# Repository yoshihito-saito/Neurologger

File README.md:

# WILD

**WILD** (Wireless, Interactive, Lightweight Datalogger) is an ultra-lightweight multimodal neurologger for long-term neural and behavioral recording in freely behaving animals. It combines local neural data logging, behavioral sensing, onboard processing, and responsive stimulation in a head-mounted platform designed for naturalistic and multi-animal experiments.

## Documentation

The documentation portal is built with MkDocs Material and is maintained through Markdown files in [`docs/`](docs/).

- [Getting Started](docs/getting-started/index.md)
- [Hardware](docs/hardware/index.md)
- [Software](docs/software/index.md)
- [Analysis](docs/analysis/index.md)
- [Community](docs/contributing.md)

## Platform Scope

- Local microSD electrophysiology recording with BLE-based control, synchronization, status, and low-bandwidth preview
- Closed-loop stimulation through embedded DSP and curated TinyML pipelines
- Current open-source 64-channel workflows, with Neuropixels-compatible and active-probe variants documented separately as research targets
- IMU, ultrasonic audio, camera, and digital event recording
- TinyML inference support through validated release-integrated models
- Long-term recording and multi-animal experiment workflows

## Repository Layout

| Path | Purpose |
| --- | --- |
| [`docs/`](docs/) | MkDocs documentation source |
| [Latest GitHub release](https://github.com/ayalab1/Neurologger/releases/latest) | Prebuilt device release images |
| [`Software/`](Software/) | WILD Console installers |
| [`Code/`](Code/) | MATLAB and Python analysis scripts |
| [`PCB/`](PCB/) | PCB fabrication and assembly files |
| [`3Dprint/`](3Dprint/) | Mechanical parts and CAD files |

## Local Documentation Build

```bash
pip install -r requirements.txt
mkdocs serve
```

The GitHub Pages workflow builds the site with:

```bash
mkdocs build --strict
```

## License

See [LICENSE](LICENSE).

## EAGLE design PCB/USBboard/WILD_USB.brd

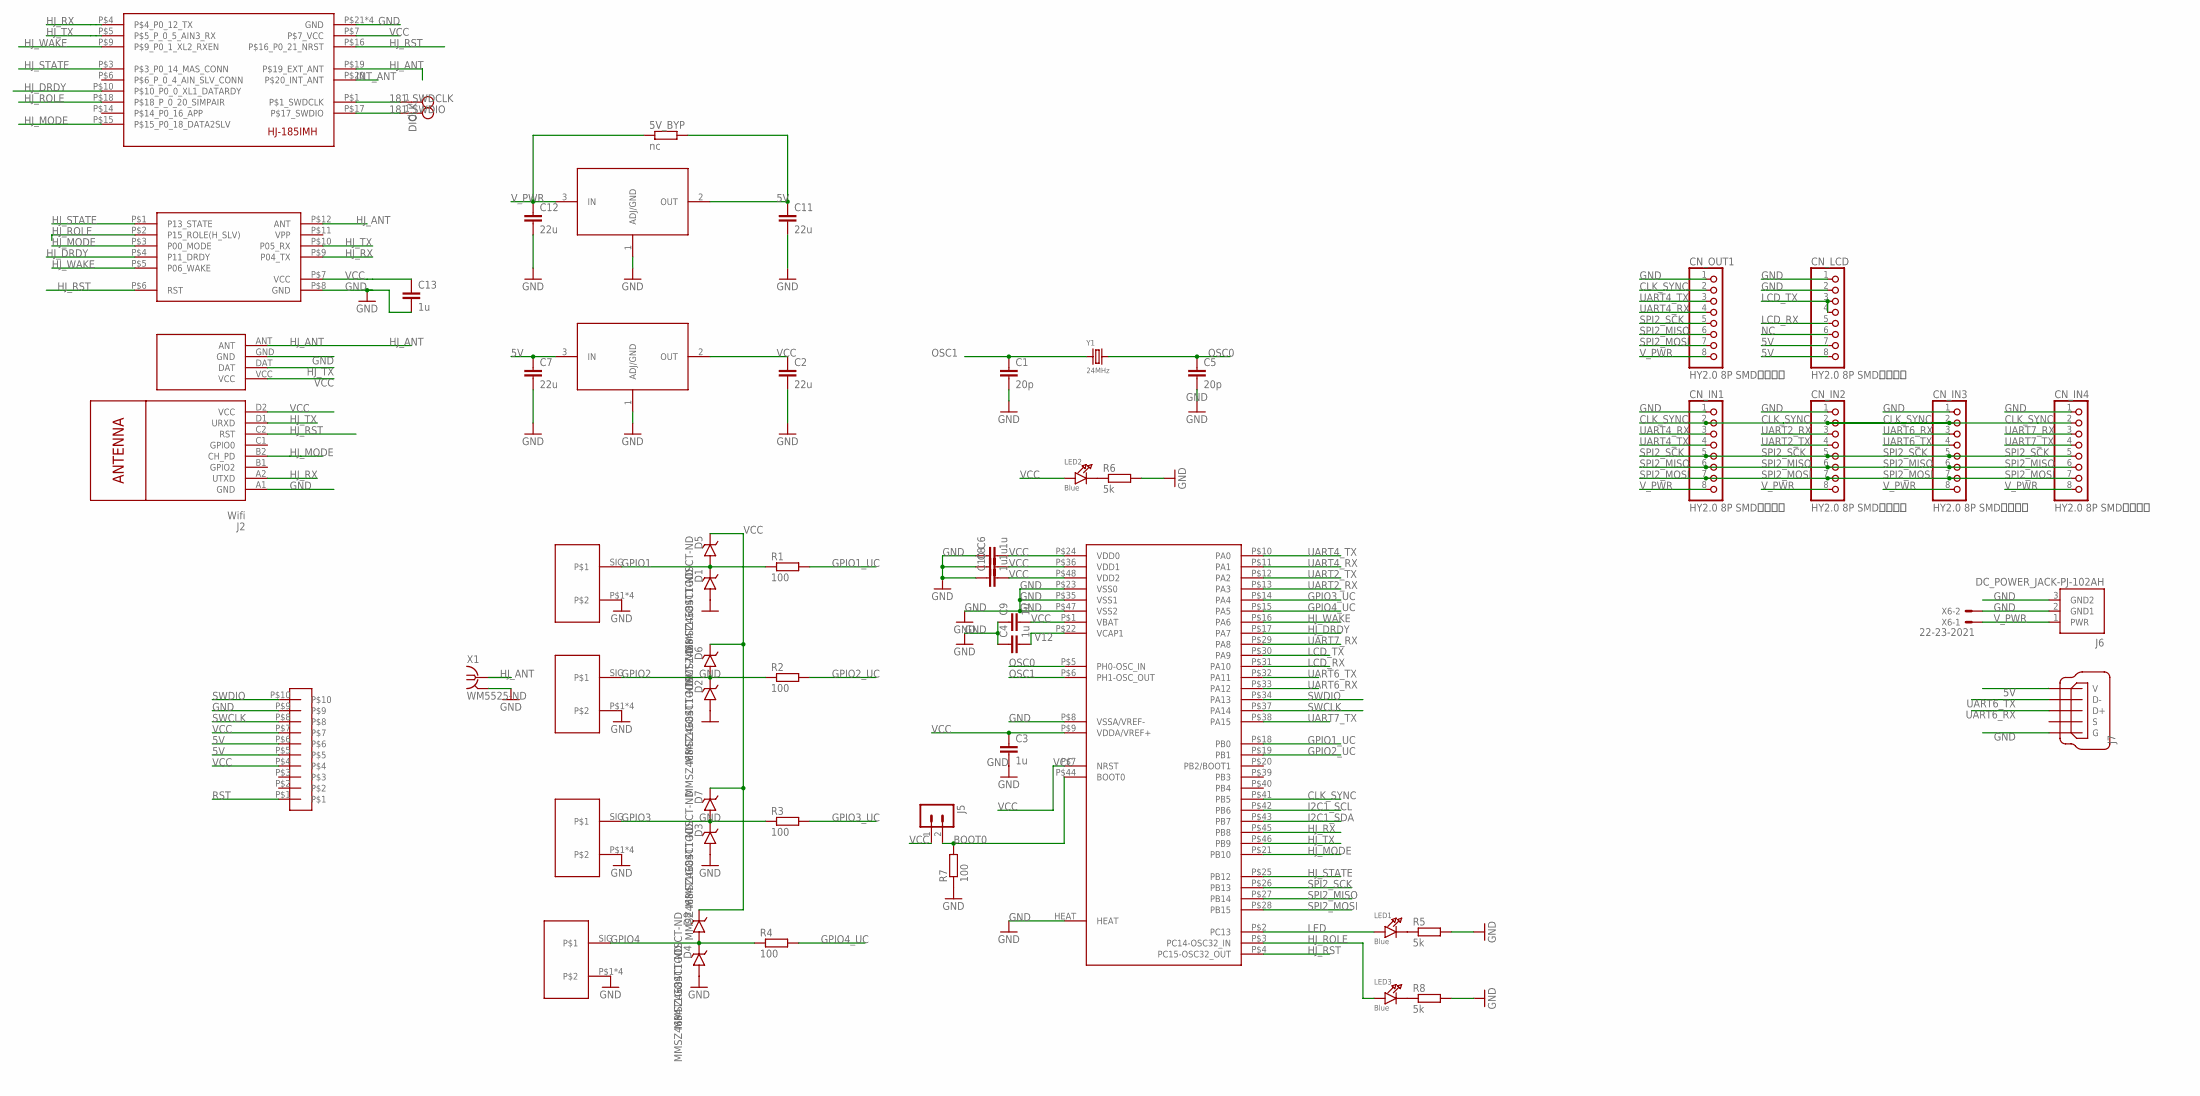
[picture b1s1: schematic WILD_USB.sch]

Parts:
5V_BYP: nc; R1206
C1, C5: 20p; C1206
C2, C7, C11, C12: 22u; C1206
C3, C4, C6, C8, C9, C10, C13: 1u; C1206
CLK: TESTPOINT_SMALL
CN_IN1, CN_IN2, CN_IN3, CN_IN4: HY2.0 8P SMD卧贴插座; JSTPH8
CN_LCD: HY2.0 8P SMD卧贴插座; JSTPH8
CN_OUT1: HY2.0 8P SMD卧贴插座; JSTPH8
D1, D2, D3, D4, D5, D6, D7, D8: MMSZ4684T1GOSCT-ND; SOD-123
DIO: TESTPOINT_SMALL
J1: Sub-GHz; SYN115
J2: Wifi; WIRELESS-WIFI-ESP-01
J3: 2*5P 2.54mm 双排母 母座; 2.54MM_2X5
J5: nc; JUMPER2
J6: DC_POWER_JACK-PJ-102AH; PJ-102AH
J7: J7; ZX62R-B-5P
LED1, LED2, LED3: Blue; CHIPLED_1206
R1, R2, R3, R4, R7: 100; R1206
R5, R6, R8: 5k; R1206
U1: STM32F413CHU6; UFQFPN48
U2: HJ580
U3: HJ_185IMHQFN; HJ_185IMH
U4: ADP3338AKCZ-3.3; SOT223
U5: nc; SOT223
X1: WM5525-ND; BU-SMA-H
X2, X3, X4, X5: BNC_8MM; BNC_V_8MM
X6: 22-23-2021
Y1: 24MHz; HC49UP

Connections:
5V: 5V_BYP.2, C7.1, C11.1, CN_LCD.7, CN_LCD.8, J3.P$5, J3.P$6, J7.1 (V), U4.3 (IN), U5.2 (OUT)
181_SWDCLK: CLK.1, U3.P$1 (P$1_SWDCLK)
181_SWDIO: DIO.1, U3.P$17 (P$17_SWDIO)
BOOT0: J5.2, R7.2, U1.P$44 (BOOT0)
CLK_SYNC: CN_IN1.2, CN_IN2.2, CN_IN3.2, CN_IN4.2, CN_OUT1.2, U1.P$41 (PB5)
GND: C1.2, C2.2, C3.2, C4.1, C5.2, C6.1, C7.2, C8.1, C9.1, C10.1, C11.2, C12.2, C13.2, CN_IN1.1, CN_IN2.1, CN_IN3.1, CN_IN4.1, CN_LCD.1, CN_LCD.2, CN_OUT1.1, D1.2 (A), D2.2 (A), D3.2 (A), D4.2 (A), J1.GND, J2.A1 (GND), J3.P$9, J6.2 (GND1), J6.3 (GND2), J7.5 (G), R5.2, R6.2, R7.1, R8.2, U1.HEAT, U1.P$8 (VSSA/VREF-), U1.P$23 (VSS0), U1.P$35 (VSS1), U1.P$47 (VSS2), U2.P$8 (GND), U3.P$21 (GND), U3.P$22 (GND), U3.P$23 (GND), U3.P$24 (GND), U4.1 (ADJ/GND), U5.1 (ADJ/GND), X1.2, X1.3 (2), X1.4 (2), X1.5 (2), X2.P$1, X2.P$2, X2.P$3, X2.P$4, X3.P$1, X3.P$2, X3.P$3, X3.P$4, X4.P$1, X4.P$2, X4.P$3, X4.P$4, X5.P$1, X5.P$2, X5.P$3, X5.P$4, X6.2
GPIO1: D1.1 (C), D5.2 (A), R1.1, X2.SIG
GPIO1_UC: R1.2, U1.P$18 (PB0)
GPIO2: D2.1 (C), D6.2 (A), R2.1, X3.SIG
GPIO2_UC: R2.2, U1.P$19 (PB1)
GPIO3: D3.1 (C), D7.2 (A), R3.1, X4.SIG
GPIO3_UC: R3.2, U1.P$14 (PA4)
GPIO4: D4.1 (C), D8.2 (A), R4.1, X5.SIG
GPIO4_UC: R4.2, U1.P$15 (PA5)
HJ_ANT: J1.ANT, U2.P$12 (ANT), U3.P$19 (P$19_EXT_ANT), X1.1
HJ_DRDY: U1.P$17 (PA7), U2.P$4 (P11_DRDY), U3.P$10 (P$10_P0_0_XL1_DATARDY)
HJ_MODE: J2.B2 (CH_PD), U1.P$21 (PB10), U2.P$3 (P00_MODE), U3.P$15 (P$15_P0_18_DATA2SLV)
HJ_ROLE: LED3.A, U1.P$3 (PC14-OSC32_IN), U2.P$2 (P15_ROLE(H_SLV)), U3.P$18 (P$18_P_0_20_SIMPAIR)
HJ_RST: J2.C2 (RST), U1.P$4 (PC15-OSC32_OUT), U2.P$6 (RST), U3.P$16 (P$16_P0_21_NRST)
HJ_RX: J2.A2 (UTXD), U1.P$45 (PB8), U2.P$9 (P04_TX), U3.P$4 (P$4_P0_12_TX)
HJ_STATE: U1.P$25 (PB12), U2.P$1 (P13_STATE), U3.P$3 (P$3_P0_14_MAS_CONN)
HJ_TX: J1.DAT, J2.D1 (URXD), U1.P$46 (PB9), U2.P$10 (P05_RX), U3.P$5 (P$5_P_0_5_AIN3_RX)
HJ_WAKE: U1.P$16 (PA6), U2.P$5 (P06_WAKE), U3.P$9 (P$9_P0_1_XL2_RXEN)
I2C1_SCL: U1.P$42 (PB6)
I2C1_SDA: U1.P$43 (PB7)
INT_ANT: U3.P$20 (P$20_INT_ANT)
LCD_RX: CN_LCD.5, U1.P$31 (PA10)
LCD_TX: CN_LCD.3, CN_LCD.4, U1.P$30 (PA9)
LED: LED1.A, U1.P$2 (PC13)
unnamed: LED3.C, R8.1
unnamed: LED1.C, R5.1
unnamed: LED2.C, R6.1
NC: CN_LCD.6
OSC0: C5.1, U1.P$5 (PH0-OSC_IN), Y1.2
OSC1: C1.1, U1.P$6 (PH1-OSC_OUT), Y1.1
RST: J3.P$1
SPI2_MISO: CN_IN1.6, CN_IN2.6, CN_IN3.6, CN_IN4.6, CN_OUT1.6, U1.P$27 (PB14)
SPI2_MOSI: CN_IN1.7, CN_IN2.7, CN_IN3.7, CN_IN4.7, CN_OUT1.7, U1.P$28 (PB15)
SPI2_SCK: CN_IN1.5, CN_IN2.5, CN_IN3.5, CN_IN4.5, CN_OUT1.5, U1.P$26 (PB13)
SWCLK: J3.P$8, U1.P$37 (PA14)
SWDIO: J3.P$10, U1.P$34 (PA13)
UART2_RX: CN_IN2.3, U1.P$13 (PA3)
UART2_TX: CN_IN2.4, U1.P$12 (PA2)
UART4_RX: CN_IN1.3, CN_OUT1.4, U1.P$11 (PA1)
UART4_TX: CN_IN1.4, CN_OUT1.3, U1.P$10 (PA0)
UART6_RX: CN_IN3.3, J7.3 (D+), U1.P$33 (PA12)
UART6_TX: CN_IN3.4, J7.2 (D-), U1.P$32 (PA11)
UART7_RX: CN_IN4.3, U1.P$29 (PA8)
UART7_TX: CN_IN4.4, U1.P$38 (PA15)
V12: C4.2, U1.P$22 (VCAP1)
VCC: C2.1, C3.1, C6.2, C8.2, C9.2, C10.2, C13.1, D5.1 (C), D6.1 (C), D7.1 (C), D8.1 (C), J1.VCC, J2.D2 (VCC), J3.P$4, J3.P$7, J5.1, LED2.A, U1.P$1 (VBAT), U1.P$7 (NRST), U1.P$9 (VDDA/VREF+), U1.P$24 (VDD0), U1.P$36 (VDD1), U1.P$48 (VDD2), U2.P$7 (VCC), U3.P$7 (P$7_VCC), U4.2 (OUT)
V_PWR: 5V_BYP.1, C12.1, CN_IN1.8, CN_IN2.8, CN_IN3.8, CN_IN4.8, CN_OUT1.8, J6.1 (PWR), U5.3 (IN), X6.1

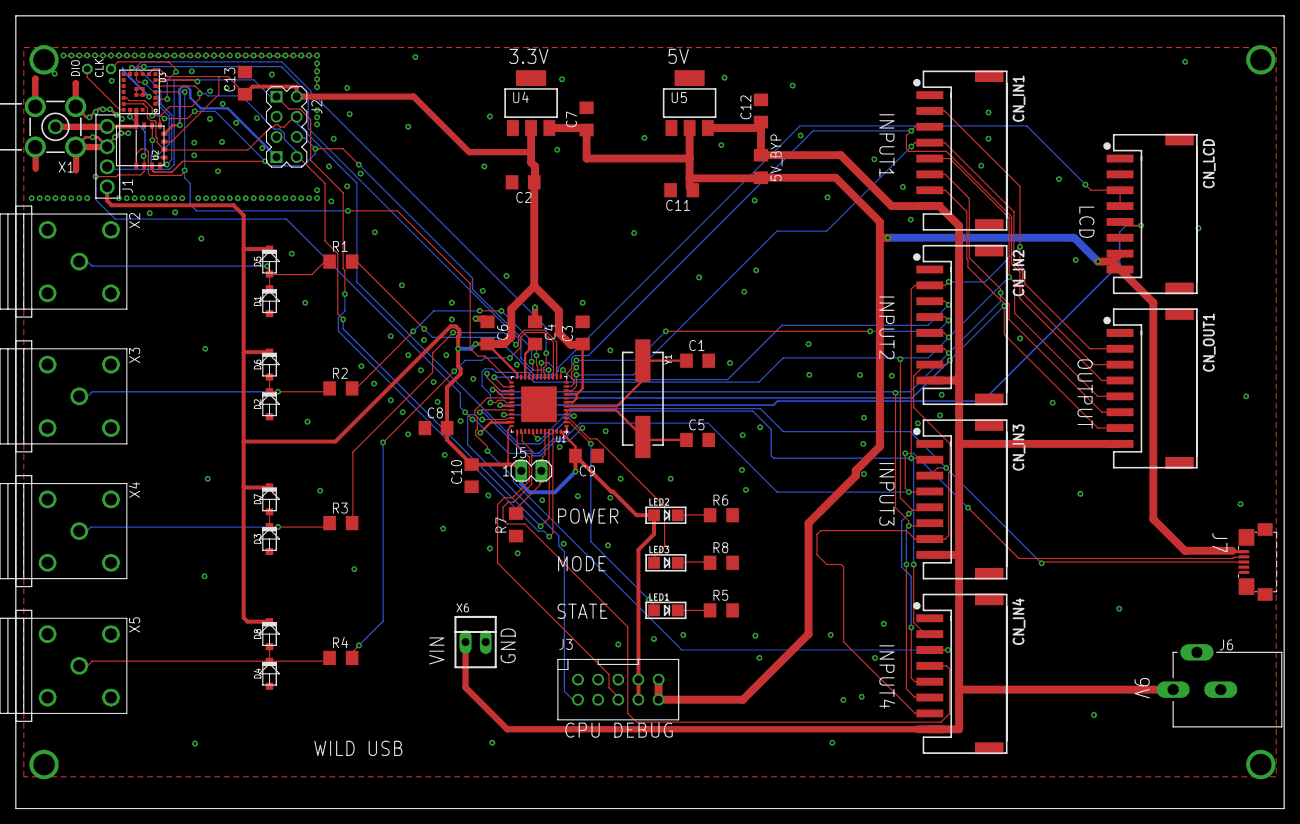
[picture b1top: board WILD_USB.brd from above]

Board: 2 copper layers, 160.0 x 100.0 mm, 59 parts (0 on the bottom side), 47 nets.

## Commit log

2026-02-13 Updated firmwares including functing bootloader
2026-05-08 WILD V45 + console V3.2.1.0
    Added two way synchronization with continuous synchronization <10ms and drift detection
    PC continueous clock calibration
    Host-follower mode:Multi-logger sample-sample synced recording
    BLE reliability
    Record file management over BLE
    Improved SD download speed
2026-06-12 Build WILD documentation site
2026-06-12 updated website
2026-06-13 updated website url
2026-06-15 Update homepage hero and fix data format table
2026-06-15 Use ephys sample image on homepage
2026-06-17 Update WILD documentation text and structure
2026-06-17 Refine WILD docs landing cards and hardware visuals
2026-06-17 Add fabrication docs and USB board package
2026-06-18 Make Windows timing prep a recording prerequisite
2026-06-22 Clean pre-publication website wording
2026-06-26 Add public soldering and rework SOP

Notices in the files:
parts and their libraries:
microbuilder: This work is placed in the public domain, and may be freely used for commercial and non-commercial work with the following conditions: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
diy-modules: Released under the Creative Commons Attribution 4.0 International License: http://creativecommons.org/licenses/by/4.0
